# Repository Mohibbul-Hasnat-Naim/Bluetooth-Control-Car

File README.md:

# Bluetooth-Control-Car
This car can be controlled via Bluetooth connectivity from a smartphone.

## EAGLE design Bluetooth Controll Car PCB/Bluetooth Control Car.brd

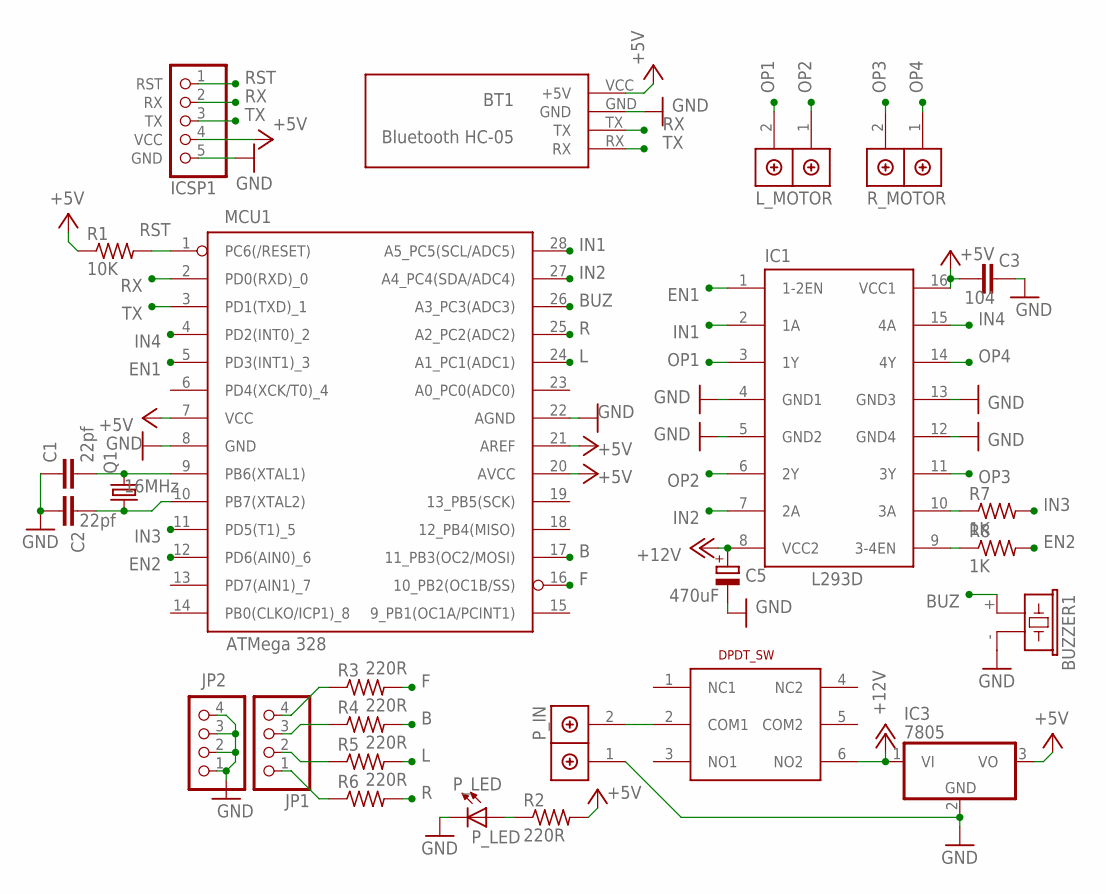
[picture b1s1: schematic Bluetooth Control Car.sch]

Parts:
BT1: Bluetooth HC-05; BLUETOOTH-HC-06-V3
BUZZER1: F/CM12P
C1, C2: 22pf; 22PF
C3: 104
C5: 470uF; E5-10,5
IC1: L293D; DIL16
IC3: 7805; TO220V
ICSP1: ICSP_ATMEGA328; ICSP_ATMEGA
JP1, JP2: PINHD-1X4; 1X04
L_MOTOR: 2P
MCU1: ATMega 328; ATMEGA328_P
P_IN: 2P
P_LED: P_LED; LED_3MM
P_SW: P_SW; 6PIN_DPDT
Q1: 16MHz; CRYSTAL
R1: 10K; THR_R_204/7
R2: 220R; THR_R_204/8
R3, R4, R5, R6: 220R; THR_R_204/7
R7, R8: 1K; THR_R_204/7
R_MOTOR: 2P

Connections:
+5V: BT1.VCC (+5V), C3.1, IC1.16 (VCC1), IC3.3 (VO), ICSP1.4 (VCC), MCU1.7 (VCC), MCU1.20 (AVCC), MCU1.21 (AREF), R1.1, R2.2
+12V: C5.+, IC1.8 (VCC2), IC3.1 (VI), P_SW.6 (NO2)
B: MCU1.17 (11_PB3(OC2/MOSI)), R4.2
BUZ: BUZZER1.+ (1), MCU1.26 (A3_PC3(ADC3))
EN1: IC1.1 (1-2EN), MCU1.5 (PD3(INT1)_3)
EN2: MCU1.12 (PD6(AIN0)_6), R8.2
F: MCU1.16 (10_PB2(OC1B/SS)), R3.2
GND: BT1.GND, BUZZER1.- (2), C1.1, C2.2, C3.2, C5.-, IC1.4 (GND1), IC1.5 (GND2), IC1.12 (GND4), IC1.13 (GND3), IC3.2 (GND), ICSP1.5 (GND), JP2.1, JP2.2, JP2.3, JP2.4, MCU1.8 (GND), MCU1.22 (AGND), P_IN.1 (CONN1), P_LED.K
IN1: IC1.2 (1A), MCU1.28 (A5_PC5(SCL/ADC5))
IN2: IC1.7 (2A), MCU1.27 (A4_PC4(SDA/ADC4))
IN3: MCU1.11 (PD5(T1)_5), R7.2
IN4: IC1.15 (4A), MCU1.4 (PD2(INT0)_2)
L: MCU1.24 (A1_PC1(ADC1)), R5.2
unnamed: C1.2, MCU1.9 (PB6(XTAL1)), Q1.2
unnamed: C2.1, MCU1.10 (PB7(XTAL2)), Q1.1
unnamed: JP1.4, R3.1
unnamed: JP1.3, R4.1
unnamed: P_LED.A, R2.1
unnamed: JP1.2, R5.1
unnamed: P_IN.2 (CONN2), P_SW.2 (COM1)
unnamed: JP1.1, R6.1
unnamed: IC1.10 (3A), R7.1
unnamed: IC1.9 (3-4EN), R8.1
OP1: IC1.3 (1Y), L_MOTOR.2 (CONN2)
OP2: IC1.6 (2Y), L_MOTOR.1 (CONN1)
OP3: IC1.11 (3Y), R_MOTOR.2 (CONN2)
OP4: IC1.14 (4Y), R_MOTOR.1 (CONN1)
R: MCU1.25 (A2_PC2(ADC2)), R6.2
RST: ICSP1.1 (RST), MCU1.1 (PC6(/RESET)), R1.2
RX: BT1.TX, ICSP1.2 (RX), MCU1.2 (PD0(RXD)_0)
TX: BT1.RX, ICSP1.3 (TX), MCU1.3 (PD1(TXD)_1)

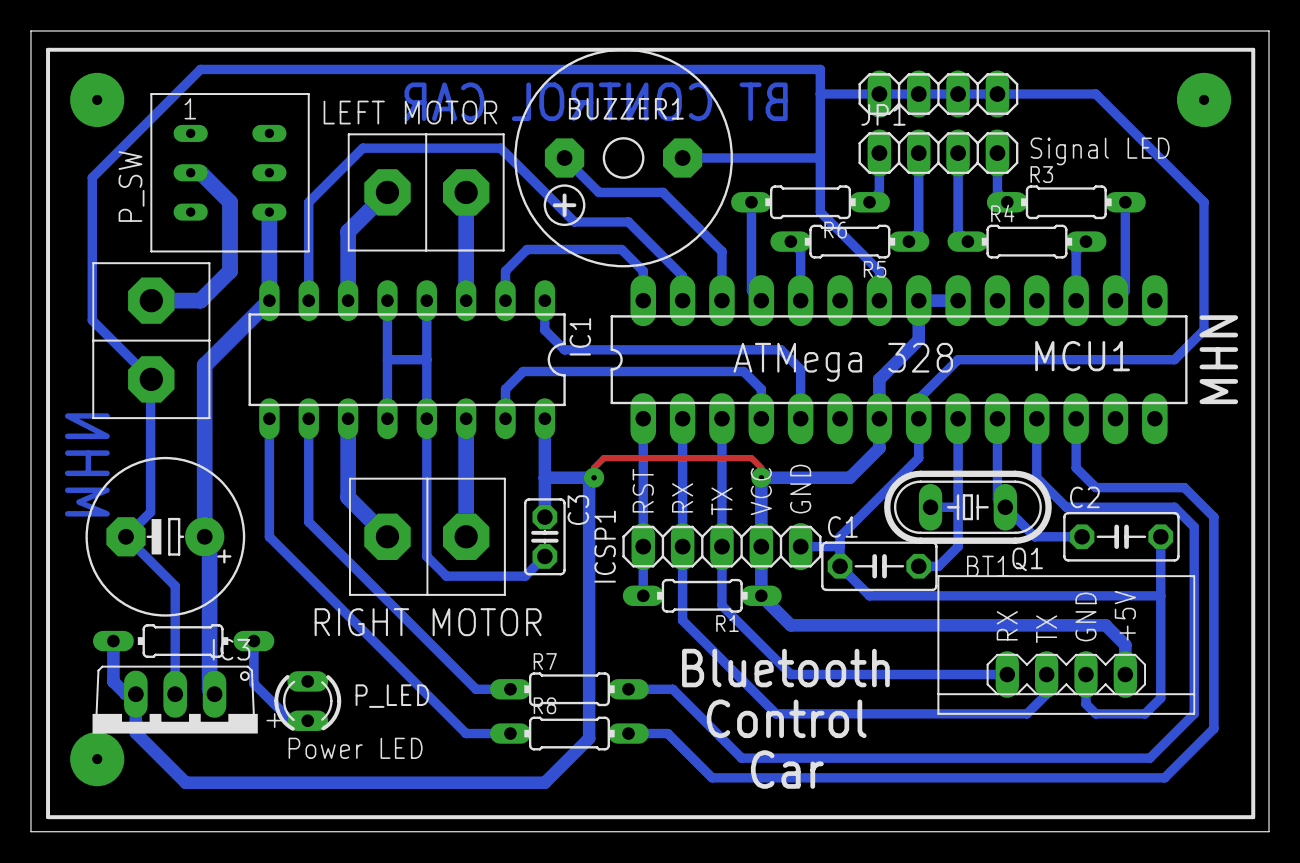
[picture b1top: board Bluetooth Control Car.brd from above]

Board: 2 copper layers, 79.9 x 51.7 mm, 26 parts (0 on the bottom side), 31 nets.
